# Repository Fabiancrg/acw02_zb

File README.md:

| Supported Targets | ESP32-C6 | ESP32-H2 |
| ----------------- |  -------- | -------- |

# ACW02-ZB Zigbee HVAC Thermostat Controller

# Project Description
ACW02-ZB is an open-source Zigbee-enabled HVAC controller for the Airton (to replace ACW02 WiFi module) series and compatible units. It allows full integration with Zigbee2MQTT, Home Assistant, and other Zigbee ecosystems, providing remote control, monitoring, and diagnostics for air conditioning systems.

### Key Features
- **Zigbee 3.0 End Device**: Compatible with ESP32-C6 and ESP32-H2
- **Full HVAC Control**: Supports on/off, mode, setpoints, fan speed, swing, eco, night, mute, and display
- **Error Diagnostics**: Exposes AC error codes and status via Zigbee attributes (Only one cade currently)
- **Automatic Polling**: Uses Z2M's generic polling framework for unreportable attributes
- **Auto-Rejoin**: Device automatically rejoins Zigbee network after removal or network loss
- **Clean Entity Names**: Optimized for Home Assistant and Zigbee2mqtt UI
- **Factory Reset**: Long-press boot button 5s for full reset
- **Open Hardware**: PCB and schematic files included (Using Seeedstudio Xiao ESP32-C6)

### Architecture
- **Firmware**: ESP-IDF C code for Zigbee stack, HVAC protocol, and attribute mapping
- **External Converter**: Custom Zigbee2MQTT JS converter for multi-endpoint mapping and polling

### Typical Use Cases
- Integrate Airton (to replace ACW02 WiFi module) with Home Assistant via Zigbee2MQTT
- Monitor and control HVAC remotely (mode, temperature, fan, swing, eco, etc.)
- Receive error codes and filter status for maintenance
- Automatic recovery from network disruptions

### Getting Started
1. Flash ESP32-C6/H2 with provided firmware
2. Add external converter to Zigbee2MQTT
3. Pair device and configure entities in Home Assistant
4. Use Z2M UI or automations for full control and monitoring

See the documentation files for advanced features, troubleshooting, and hardware details.

### ZHA Support (untested)

The device should also be compatible with **ZHA (Zigbee Home Automation)**. Because it uses standard Zigbee 3.0 clusters, core functionality (climate control, switches) works out of the box. A custom ZHA quirk (`acw02_zb.py`) is provided to handle the non-standard fan mode values and the full 9-endpoint structure.

> **Warning:** ZHA support has **not been tested**. The quirk is provided as a best-effort implementation based on the device's Zigbee descriptor and firmware source. Feedback and contributions are welcome.

> **Note:** Some features available in Zigbee2MQTT require additional HA automations under ZHA — see the [ZHA Integration Guide](ZHA_INTEGRATION_GUIDE.md) for installation steps, known limitations, and workarounds.

---

## PCB

The PCB has been tested for a couple of weeks now on 4 units and is working well.
I am using a Seeedstudio Xiao ESP32-C6 with a custom buck converter (based on a MPS MP1584) and a level shifter for TX/RX (using a Texas Instrument TXB0102)

PCB is small, 48mm x 27mm so there is no problem to fit it inside the unit.
---

## 🙌 Credits

- Original HVAC reverse‑engineering and ESPHome work: [devildant/acw02_esphome](https://github.com/devildant/acw02_esphome)  
- Zigbee2MQTT ecosystem: [Koenkk/zigbee2mqtt](https://github.com/Koenkk/zigbee2mqtt) and [zigbee-herdsman-converters](https://github.com/Koenkk/zigbee-herdsman-converters)

## 🛡️ License

This repository uses multiple licenses depending on content type:

- **Code** (`*.yaml`, `*.cpp`, `*.h`) — [GNU GPLv3](./LICENSE)  
- **PCB files** (`*.zip`, `*.json`) — [CC BY-NC-SA 4.0](./LICENSE-hardware)

---

# ⚠️ Disclaimer

This project is provided as-is, without any warranty or guarantee of fitness for a particular purpose. Use at your own risk. The authors and contributors are not responsible for any damage, malfunction, or loss resulting from the use, modification, or installation of this hardware or software.

- This is an open-source, community-driven project intended for educational and experimental use.
- The hardware and firmware are not certified for commercial or safety-critical applications.
- Always follow proper electrical safety procedures when working with HVAC systems and mains power.
- Modifying or installing this project may void your equipment warranty.
- Ensure compliance with local laws and regulations regarding wireless devices and HVAC modifications.

By using this project, you acknowledge and accept these terms.

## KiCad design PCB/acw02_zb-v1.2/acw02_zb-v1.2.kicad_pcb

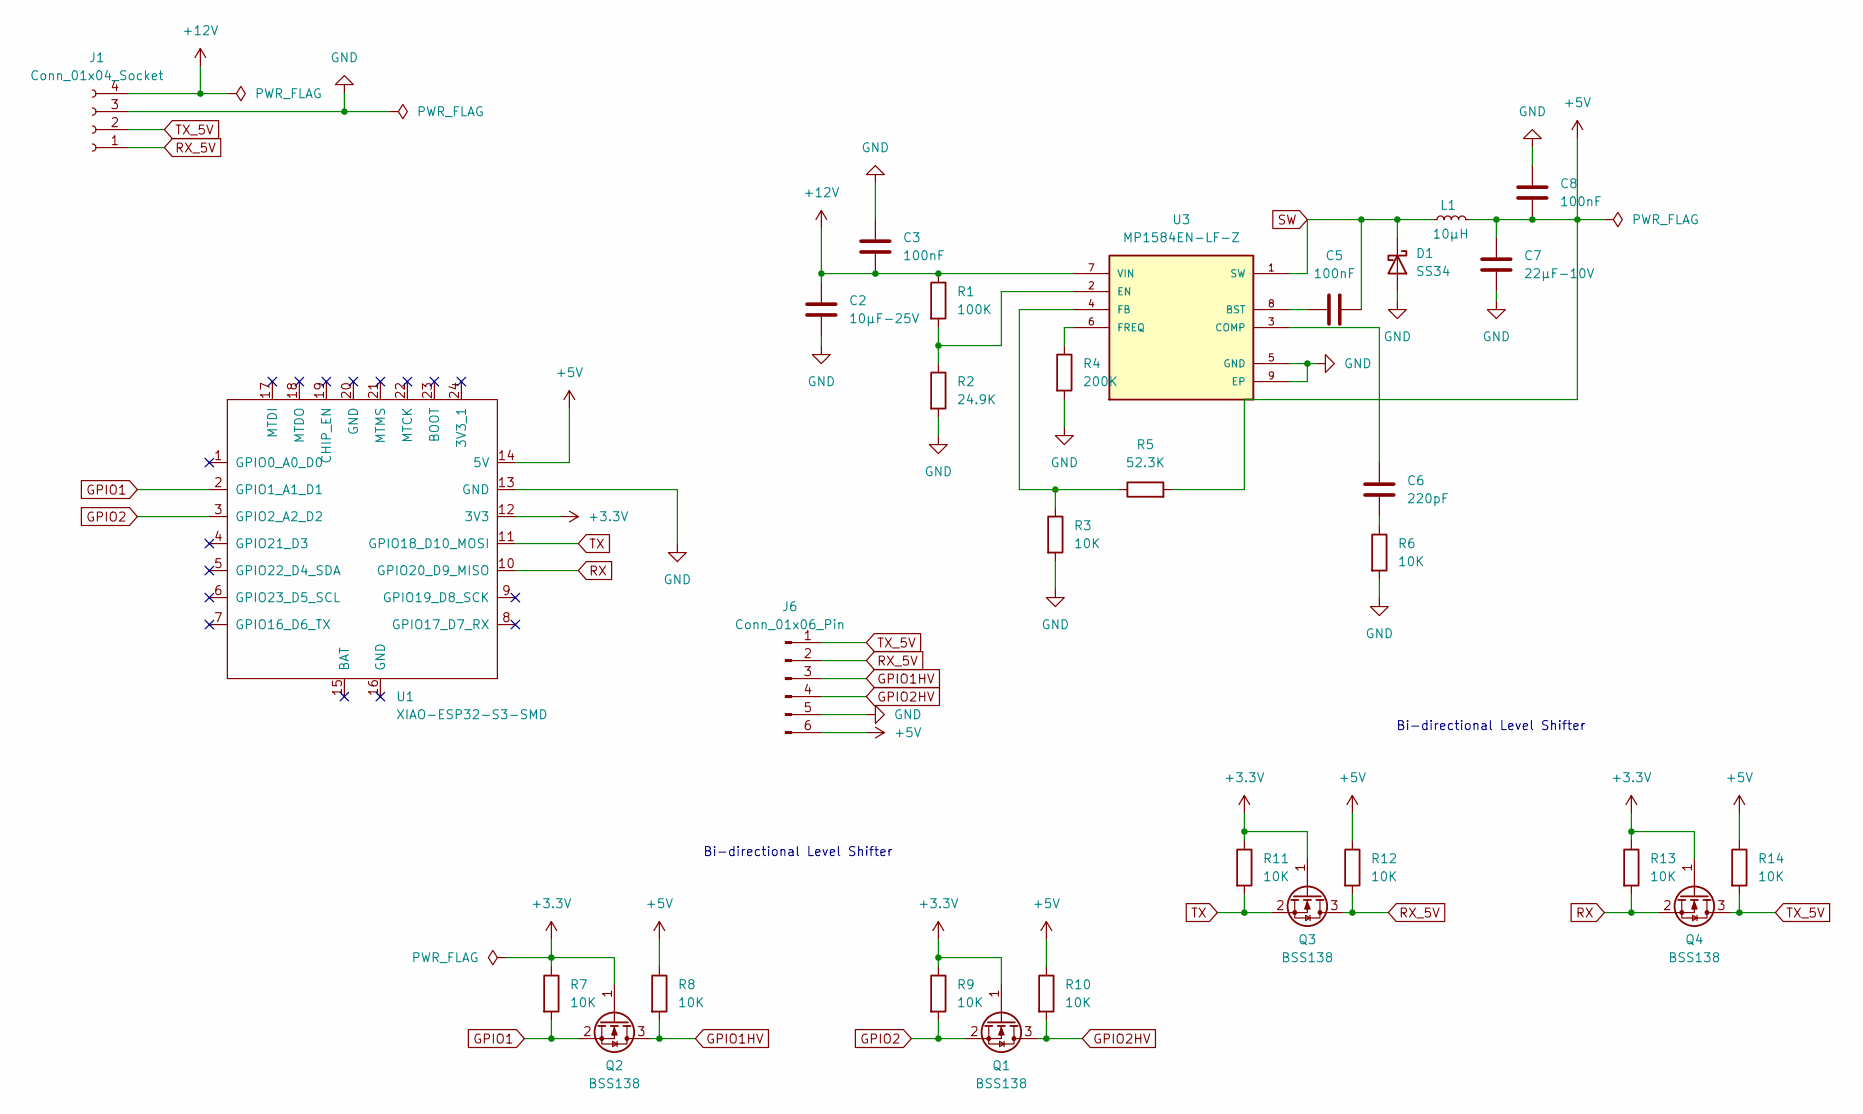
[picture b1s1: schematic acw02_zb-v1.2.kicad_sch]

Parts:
C2: 10µF-25V; C_1206_3216Metric
C3, C5, C8: 100nF; C_1206_3216Metric
C6: 220pF; C_0805_2012Metric
C7: 22µF-10V; C_1206_3216Metric
D1: SS34; D_SMA
J1: Conn_01x04_Socket; JST_XH_S4B-XH-A_1x04_P2.50mm_Horizontal
J6: Conn_01x06_Pin; JST_SH_BM06B-SRSS-TB_1x06-1MP_P1.00mm_Vertical
L1: 10µH; L_APV_APH0530
Q1, Q2, Q3, Q4: BSS138; SOT-23
R1: 100K; R_0805_2012Metric
R2: 24.9K; R_0805_2012Metric
R3, R6, R7, R8, R9, R10, R11, R12, R13, R14: 10K; R_0805_2012Metric
R4: 200K; R_0805_2012Metric
R5: 52.3K; R_0805_2012Metric
U1: XIAO-ESP32-S3-SMD; XIAO-ESP32C6-SMD
U3: MP1584EN-LF-Z; SOIC-8-1EP_3.9x4.9mm_P1.27mm_EP2.29x3mm

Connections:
+3.3V: Q1.1 (G), Q2.1 (G), Q3.1 (G), Q4.1 (G), R7.1, R9.1, R11.1, R13.1, U1.12 (3V3)
+5V: C7.1, C8.1, J6.6, L1.2, R5.2, R8.1, R10.1, R12.1, R14.1, U1.14 (5V)
+12V: C2.1, C3.1, J1.4, R1.1, U3.7 (VIN)
GND: C2.2, C3.2, C7.2, C8.2, D1.2 (A), J1.3, J6.5, R2.2, R3.2, R4.2, R6.2, U1.13 (GND), U3.5 (GND), U3.9 (EP)
GPIO1: Q2.2 (S), R7.2, U1.2 (GPIO1_A1_D1)
GPIO1HV: J6.3, Q2.3 (D), R8.2
GPIO2: Q1.2 (S), R9.2, U1.3 (GPIO2_A2_D2)
GPIO2HV: J6.4, Q1.3 (D), R10.2
unnamed: C6.2, R6.1
unnamed: C5.1, U3.8 (BST)
unnamed: C6.1, U3.3 (COMP)
unnamed: R1.2, R2.1, U3.2 (EN)
unnamed: R3.1, R5.1, U3.4 (FB)
unnamed: R4.1, U3.6 (FREQ)
RX: Q4.2 (S), R13.2, U1.10 (GPIO20_D9_MISO)
RX_5V: J1.1, J6.2, Q3.3 (D), R12.2
SW: C5.2, D1.1 (K), L1.1, U3.1 (SW)
TX: Q3.2 (S), R11.2, U1.11 (GPIO18_D10_MOSI)
TX_5V: J1.2, J6.1, Q4.3 (D), R14.2

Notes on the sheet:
Bi-directional Level Shifter

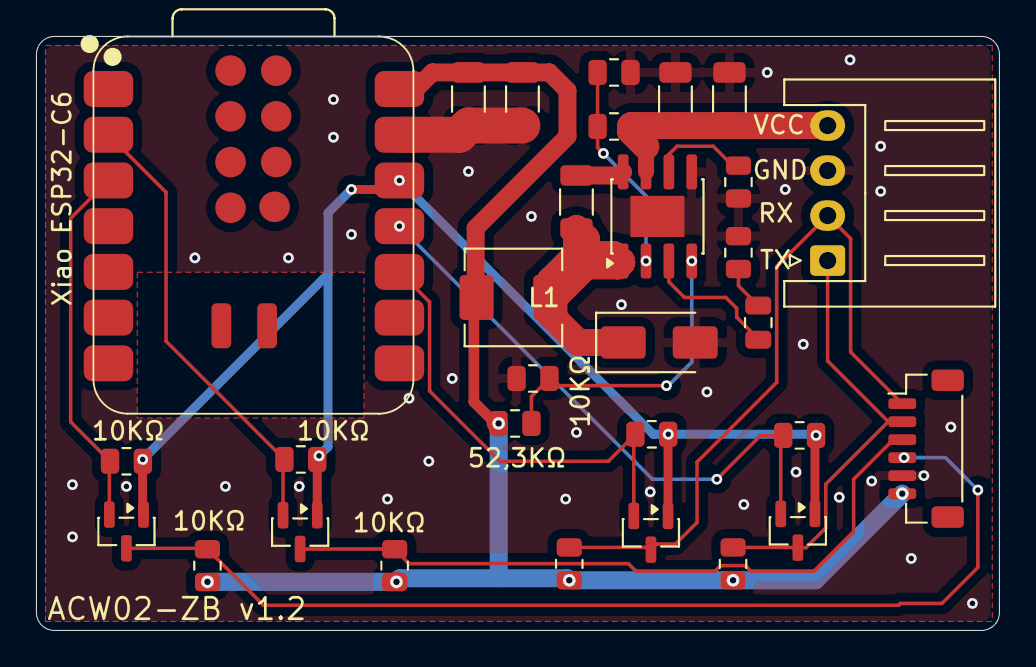
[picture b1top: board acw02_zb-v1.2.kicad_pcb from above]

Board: 2 copper layers, 53.5 x 33.0 mm, 30 parts (0 on the bottom side), 19 nets.

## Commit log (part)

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2025-10-13 Initial commit for acw02_zb
2025-10-13 modified: .gitignore
2025-10-13 First version
2025-10-13 Some updates but still issues
2025-10-13 Corrected Zigbee strings
2025-10-13 Add ECO, Swing and Display on/ff
2025-10-13 Logging updated
2025-10-13 Reset button use interrupt instead of polling
2025-10-13 Problem Solved: UART Pin Conflict The Issue Your console was freezing at "Boot button initiali�" because:
    HVAC driver was using GPIO 16 & 17
    These are the same pins as the console UART (UART0)
    When HVAC driver called uart_set_pin(), it disconnected the console
2025-10-13 Z2M Custom Switch Converters Added
2025-10-13 Fixed: Changed from Write to Command
2025-10-13 Added Fan Mode to Attribute Updates
2025-10-13 Problem: ACW02 has 8 speeds, but Zigbee standard has 7 fan modes
    Solution: Map the 8 ACW02 speeds to the 7 Zigbee modes intelligently:
    Z2M Selection → ACW02 Speed
    off → SILENT (Quiet mode)
    low → P20 (20%)
    medium → P60 (60%)
    high → P100 (100%)
2025-10-13 Correct issues when interviewing device
2025-10-13 Correct communication protocol
2025-10-13 Add new EP (NIGHT, PURIFIER, CLEAN and MUTE) Add Night mode switch (Endpoint 5) Add Purifier switch (Endpoint 6) Add Clean status as binary sensor (Endpoint 7) Add Mute switch (Endpoint 8)
2025-10-13 More doc + rename library file
2025-10-14 Most of the featues are working. Remaining issues with: - Local temperature (Endpoint: ep1) : Not updated - Running state (Endpoint: ep1) : Stays NULL - settings are not saved when power is cut - Pow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
2025-10-14 Running state (Endpoint: ep1)
2025-10-14 Add feature to save settings in NVS + Report local temp and mode
2025-10-14 Updated current mode
2025-10-14 Summary of what we've accomplished:
    ✅ Running State - Added running_mode attribute to thermostat cluster, properly mapped all HVAC modes
    ✅ Local Temperature - Fixed converter to publish local_temperature_ep1 with proper suffix
    ✅ NVS Persistence - Settings now save to flash and restore on power cycle
    ✅ 13-byte ACK frames - Properly handled to eliminate warnings
    ✅ Z2M Converter - Custom thermostat_ep1 converter with proper _ep# suffixes
    ✅ Clean MQTT payload - Removed duplicate property names
2025-10-14 Add Endpoint 9 - Error Diagnostics Binary Sensor created with:
    Binary status: ON when error/warning present, OFF when clear
    Error text: Human-readable error description (up to 64 characters)
    Custom attribute 0x8000: Zigbee string containing the error message
    ✅ Error Code Lookup Table (53 codes from your CSV):
    Maps error codes like E1, P4, U0, etc. to descriptions
    Example: 0xE1 → "Overload protection"
2025-10-14 Update error handling on EP9
2025-10-14 Fix logging bug for ambient temp
2025-10-14 Fix converter (remove EP9)
2025-10-14 Fix reporting
2025-10-14 Try to fix running mode and Error Text
2025-10-14 Check if attribute runningState is reportable
2025-10-14 Remove runningState keep runningMode
2025-10-14 Update Z2M Polling in converter
2025-10-14 Update converter
2025-10-15 Attemp ti fix polling
2025-10-15 Update EP names (remove _ep#)
2025-10-15 Update EP
2025-10-15 Updated converter
2025-10-15 Add more logging to polling part
2025-10-15 Change Clean status to binary sensor
2025-10-15 Fix error
2025-10-15 Polling still not working
2025-10-15 Add LICENSE file with GPL v3.0 details
2025-10-15 Add hardware license under CC BY-NC-SA 4.0
    This file outlines the licensing terms for hardware design files in the repository.
2025-10-15 Add auto-rejoin after leaving the network
2025-10-15 Add license section to README
    Added license information for code and PCB files.
2025-10-15 Add credits for HVAC and Zigbee2MQTT contributions
    Added credits section for original work and contributors.
2025-10-15 Rename project and enhance license section
    Updated project title and reorganized license information.
2025-10-15 Clean project folder
2025-10-15 Add Ko-fi support button to README
2025-10-15 Revise project title and include license information
    Updated project title and added license badges.
2025-10-15 Refactor Credits section in README.md
2025-10-15 Add Ko-fi username for funding support
2025-10-16 Update converter to have only one setpoint AC unit does not have a different setpoint for heating our cooling
2025-10-16 Add error endpoint (Bianry R/O) and device is now a router
2025-10-16 removing log file
2025-10-16 Update polling mechanism to working version
2025-10-17 Fix bugs in converter and firmware
2025-10-18 Chnage GPIO for RX/TX (Xiao ESP32-C6)
2025-10-18 Correct PIN number
2025-10-21 Add Gerber file (ordered placed but not tested)
2025-10-21 Add PCB image
2025-10-21 Document PCB details and components used
    Added section about PCB details including components and image.
2025-10-29 Add OTA support
2025-10-29 Enhance OTA functionality by adding client-specific attributes and improving status handling
2025-10-29 Remove unecessary functions
2025-10-29 Update converter to support OTA feature
2025-10-29 Change board type (Devkit with 8MB flash)
2025-10-29 Update OTA : Add console logging
2025-10-29 Update baord config to ESP32-C6-DEVKit
2025-10-29 Test OTA using same SW but with version 1.0.1
2025-10-30 Update project version to 1.0.0 and enhance OTA support with versioning attributes
2025-10-30 Update project version to 1.1 and enhance OTA configuration with new parameters
2025-10-30 Update build number to 20 and enable OTA logging for debugging
2025-10-30 Update build number to 30 and modify OTA image generation command
2025-10-30 Enhance OTA functionality with detailed logging and upgrade handling
2025-10-30 Remove manual command comments from OTA image generation target
2025-10-30 Refactor OTA version handling in CMakeLists.txt and enhance logging in esp_zb_ota.c
2025-10-31 Refactor OTA version hex string generation in CMakeLists.txt
2025-10-31 Add OTA app validity check and update partition sizes in configuration
2025-10-31 Implement OTA validation logic with detailed logging and state management
2025-11-01 Added the missing call to ota_validation_zigbee_connected() in the network steering success handler.
2025-11-01 Add OTA validation function declarations in esp_zb_hvac.c
2025-11-01 Update OTA handling with new callback functions and increment build number
2025-11-02 Bump project version to 1.2 and reset build number; enhance OTA handling with improved logging and validation; update partition sizes for optimized OTA updates
2025-11-02 Enhance OTA validation logic and update logging configuration in sdkconfig.defaults
2025-11-03 Update project version to 1.3, reset build number, and enhance logging configuration; add board-specific antenna switching definitions
2025-11-04 Update board to ESP32-C6 with LP core
2025-11-04 Update build number to 10 and set IDF init version to 5.5.1; adjust logging configuration
2025-11-07 Fix typo in definition: change 'oota' to 'ota'
2025-11-12 Enhance HVAC Zigbee clusters with REPORTING flag for improved attribute persistence and add debug verification for reporting status
2025-11-13 Refine HVAC state polling logic to detect changes and update Zigbee attributes conditionally; enhance logging for state changes and adjust TX power logging frequency
2025-11-13 Rename picture file
2025-11-13 Refactor HVAC temperature comparison to use fabsf for improved accuracy; update sdkconfig for optimization settings
2025-11-13 Update BUILD_NUMBER to 10 for versioning consistency
2025-11-15 Enable debug optimization and assertions in sdkconfig for improved build diagnostics
2025-11-15 Update version to 1.5 and reset BUILD_NUMBER; implement delayed NVS save to reduce flash wear
2025-11-20 Create PCB version 1.1 - Add two level shifters (as same board will be used for PC-1001 Heat pump controller) - Clear zone around the antenna
2025-11-20 Update .gitignore to remove unecessary PCB files
2025-11-20 Update .gitignore to exclude additional PCB backup files and remove lock file
2025-11-21 Update HVAC driver to implement state change callback and adjust temperature encoding
2025-11-21 Update HVAC driver to notify Zigbee layer only on state changes; enhance logging for running mode calculations and state updates
2025-11-21 Update HVAC driver to set Zigbee attribute values without notifying on each change, let reporting do its work
2025-11-21 Update HVAC driver to prevent notifying on attribute changes for running mode and fan mode
2025-11-22 Update version configuration and manufacturer name in CMakeLists and esp_zb_hvac header
2025-11-22 Update ACW02 HVAC Thermostat converter to support custom devices (DiY)
2025-11-22 Update build number and manufacturer name in CMakeLists and esp_zb_hvac header
2025-11-23 Refactor code structure for improved readability and maintainability
2025-11-23 Updte Zigbee2mqtt converter file custom_devices_diy.ts to add support for ACW02
2025-11-25 Update HVAC driver to replace filter_dirty with clean_status and adjust build number in CMakeLists
2025-11-25 Remove filter_dirty check from HVAC state decoding logic
2025-11-25 Add initial project files for acw02_zb PCB version 1.2
2025-12-03 Add backup directory for ACW02 PCB version 1.2 to .gitignore
2025-12-10 Update CMakeLists and sdkconfig files for path corrections and configuration adjustments
2025-12-11 Update CMakeLists and sdkconfig for Zigbee OTA image generation and flash configuration
2026-03-07 Update README_HVAC.md to require ESP-IDF v5.5.3 or later
2026-03-07 Update CMakeLists.txt to reference new Zigbee zcl_utility paths and add error handling
2026-03-07 Update HVAC driver to add error handling and mutex for state management
2026-04-03 Add ZHA support for ACW02-ZB HVAC Thermostat with custom quirk implementation
2026-04-03 Update PCB files (pictures) for ACW02-ZB
2026-04-03 Add bill of materials for ACW02-ZB

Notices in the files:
README.md:
License: GPL v3
License: CC BY-NC-SA 4.0
